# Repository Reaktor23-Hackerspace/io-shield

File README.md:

# IO-shield

IO-shield is a Arduino shield with 8 LED's, 8 push buttons and 2 potentiometers, designed for learning purposes.

# Pictures

# Example program

Open and upload the example program with the Arduino IDE. Each button triggers a LED blink pattern. 
The program is for test purposes to test all components on the board (except for the 2 potentiometers).

 - Button 1 : All LED's off
 - Button 2 : All LED's on
 - Button 3 : All LED's blink
 - Button 4 : Knightrider
 - Button 5 : Chaser
 - Button 6 : VU Meter
 - Button 7 : Random blink
 - Button 8 : Bounce

Note: You need to press the buttons for about 2 seconds in the worst case to trigger a pattern change.

# Wiring

 - Push button 1 : Arduino Pin 11
 - Push button 2 : Arduino Pin 10
 - Push button 2 : Arduino Pin 9
 - Push button 4 : Arduino Pin 8
 - Push button 5 : Arduino Pin 7
 - Push button 6 : Arduino Pin 6
 - Push button 7 : Arduino Pin 5
 - Push button 8 : Arduino Pin 4

 - LED 1 : Arduino Pin 3
 - LED 2 : Arduino Pin 2
 - LED 3 : Arduino Pin A0
 - LED 4 : Arduino Pin A1
 - LED 5 : Arduino Pin A2
 - LED 6 : Arduino Pin A3
 - LED 7 : Arduino Pin A4
 - LED 8 : Arduino Pin A5

# Partlist

## Reichelt

 Part name      | Part type                                                                    | Part price (EUR) 
--------------- | ---------------------------------------------------------------------------- | ---------------- 
LED1 - LED8     | [SMD-LED 3528 BL](http://www.reichelt.de/index.html?ACTION=3;ARTICLE=46297)  | 0.25 
R9 - R16        | [SMD 1/4W 220](http://www.reichelt.de/index.html?ACTION=3;ARTICLE=18287)     | 0.103
R1 - R8         | [SMD 1/4W 10K](http://www.reichelt.de/index.html?ACTION=3;ARTICLE=18244)     | 0.103
JP1 - JP16      | [SL 1X36G 2,54](http://www.reichelt.de/index.html?ACTION=3;ARTICLE=19504)    | 0.15
                | [JUMPER 2,54GL SW](http://www.reichelt.de/index.html?ACTION=3;ARTICLE=9019)  | 0.04
S1 - S8         | [TASTER 9314](http://www.reichelt.de/index.html?ACTION=3;ARTICLE=44510)      | 0.20

## dirtypcbs.com

- PCB 20Stk.        10x10cm + DHL HongKong = 75$ (58.88 EUR)

## Ebay

- Pin Header 6x                       0.15 EUR      2 pcs. / board
- Pin header 8x                       0.15 EUR      3 pcs. / board

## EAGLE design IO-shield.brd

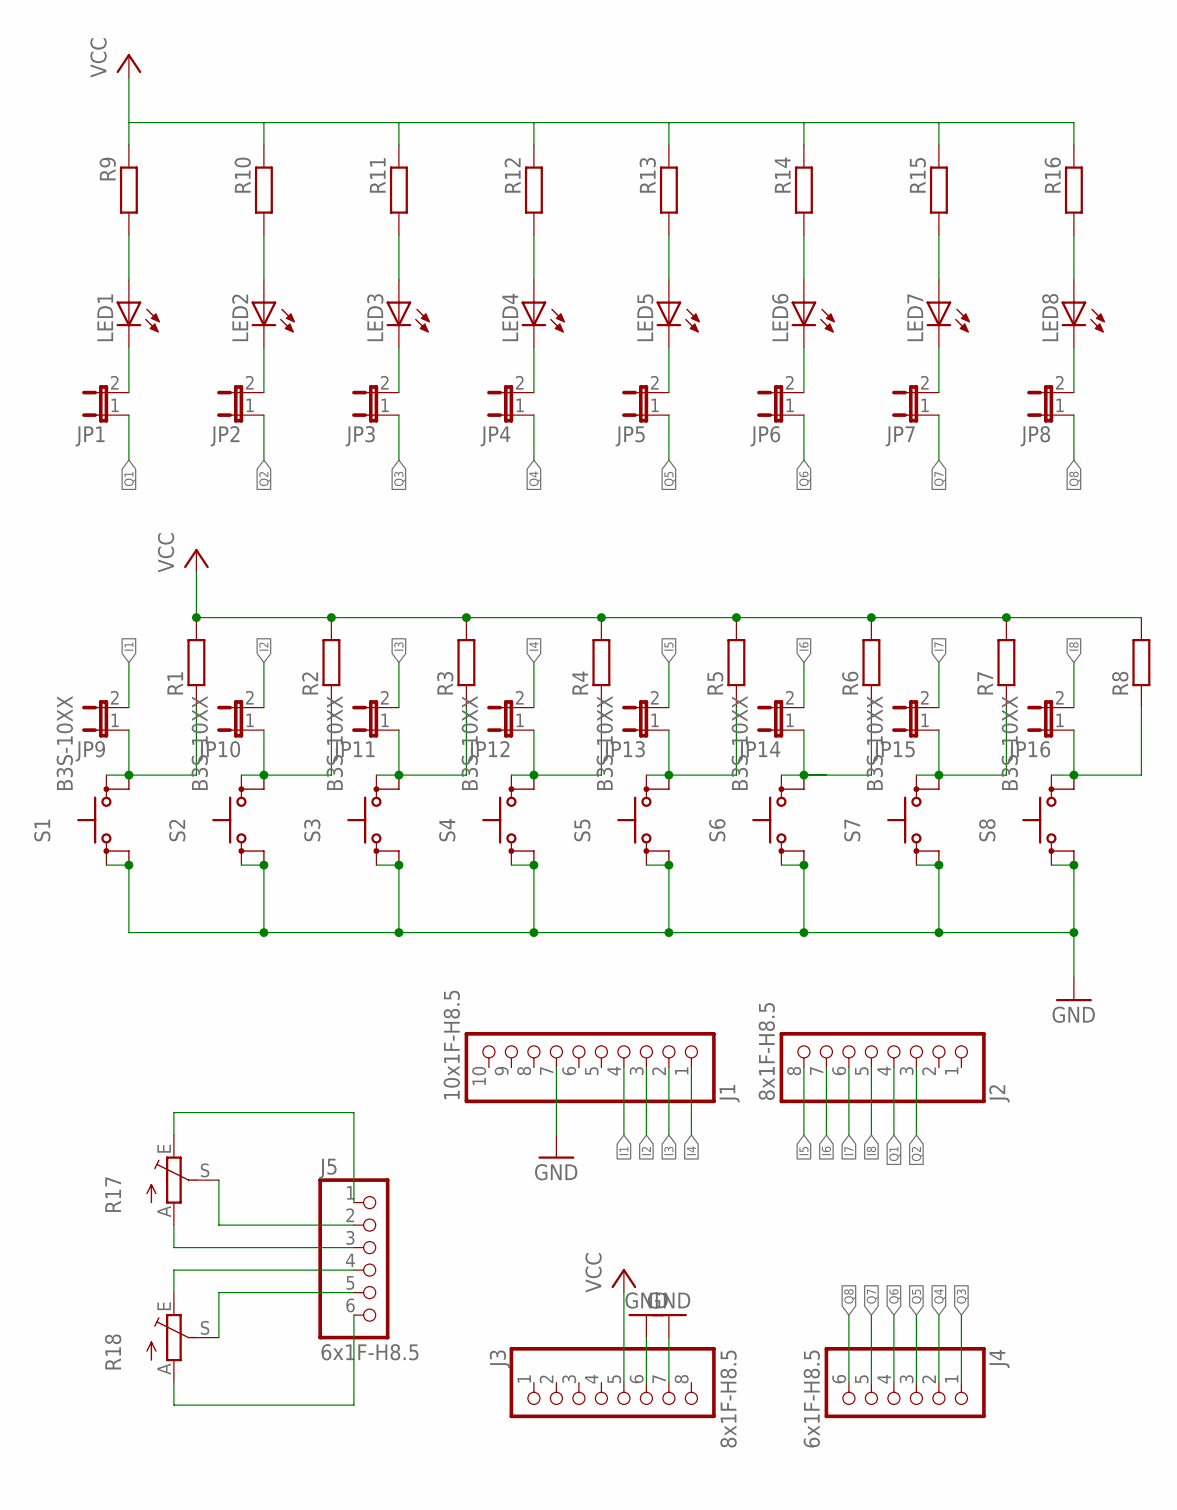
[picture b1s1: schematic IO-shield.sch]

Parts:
J1: 10x1F-H8.5; 1X10
J2, J3: 8x1F-H8.5; 1X08
J4, J5: 6x1F-H8.5; 1X06
JP1, JP2, JP3, JP4, JP5, JP6, JP7, JP8, JP9, JP10, JP11, JP12, JP13, JP14, JP15, JP16: JP1E; JP1
LED1, LED2, LED3, LED4, LED5, LED6, LED7, LED8: LEDKA-3528ASYC; KA-3528ASYC
R1, R2, R3, R4, R5, R6, R7, R8, R9, R10, R11, R12, R13, R14, R15, R16: R-EU_M1206; M1206
R17, R18: TRIM_EU-CA6V; CA6V
S1, S2, S3, S4, S5, S6, S7, S8: B3S-10XX

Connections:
GND: J1.7, J3.6, J3.7, S1.1, S1.2 (P1), S2.1, S2.2 (P1), S3.1, S3.2 (P1), S4.1, S4.2 (P1), S5.1, S5.2 (P1), S6.1, S6.2 (P1), S7.1, S7.2 (P1), S8.1, S8.2 (P1)
I1: J1.4, JP9.2
I2: J1.3, JP10.2
I3: J1.2, JP11.2
I4: J1.1, JP12.2
I5: J2.8, JP13.2
I6: J2.7, JP14.2
I7: J2.6, JP15.2
I8: J2.5, JP16.2
unnamed: JP1.2, LED1.C
unnamed: JP2.2, LED2.C
unnamed: JP9.1, R1.1, S1.3 (S), S1.4 (S1)
unnamed: JP10.1, R2.1, S2.3 (S), S2.4 (S1)
unnamed: JP11.1, R3.1, S3.3 (S), S3.4 (S1)
unnamed: JP12.1, R4.1, S4.3 (S), S4.4 (S1)
unnamed: JP13.1, R5.1, S5.3 (S), S5.4 (S1)
unnamed: JP14.1, R6.1, S6.3 (S), S6.4 (S1)
unnamed: LED1.A, R9.2
unnamed: LED2.A, R10.2
unnamed: LED3.A, R11.2
unnamed: LED4.A, R12.2
unnamed: LED5.A, R13.2
unnamed: LED6.A, R14.2
unnamed: LED7.A, R15.2
unnamed: LED8.A, R16.2
unnamed: JP15.1, R7.1, S7.3 (S), S7.4 (S1)
unnamed: JP16.1, R8.1, S8.3 (S), S8.4 (S1)
unnamed: JP3.2, LED3.C
unnamed: JP4.2, LED4.C
unnamed: JP5.2, LED5.C
unnamed: JP6.2, LED6.C
unnamed: JP7.2, LED7.C
unnamed: JP8.2, LED8.C
unnamed: J5.2, R17.S
unnamed: J5.1, R17.E
unnamed: J5.3, R17.A
unnamed: J5.5, R18.S
unnamed: J5.4, R18.E
unnamed: J5.6, R18.A
Q1: J2.4, JP1.1
Q2: J2.3, JP2.1
Q3: J4.1, JP3.1
Q4: J4.2, JP4.1
Q5: J4.3, JP5.1
Q6: J4.4, JP6.1
Q7: J4.5, JP7.1
Q8: J4.6, JP8.1
VCC: J3.5, R1.2, R2.2, R3.2, R4.2, R5.2, R6.2, R7.2, R8.2, R9.1, R10.1, R11.1, R12.1, R13.1, R14.1, R15.1, R16.1

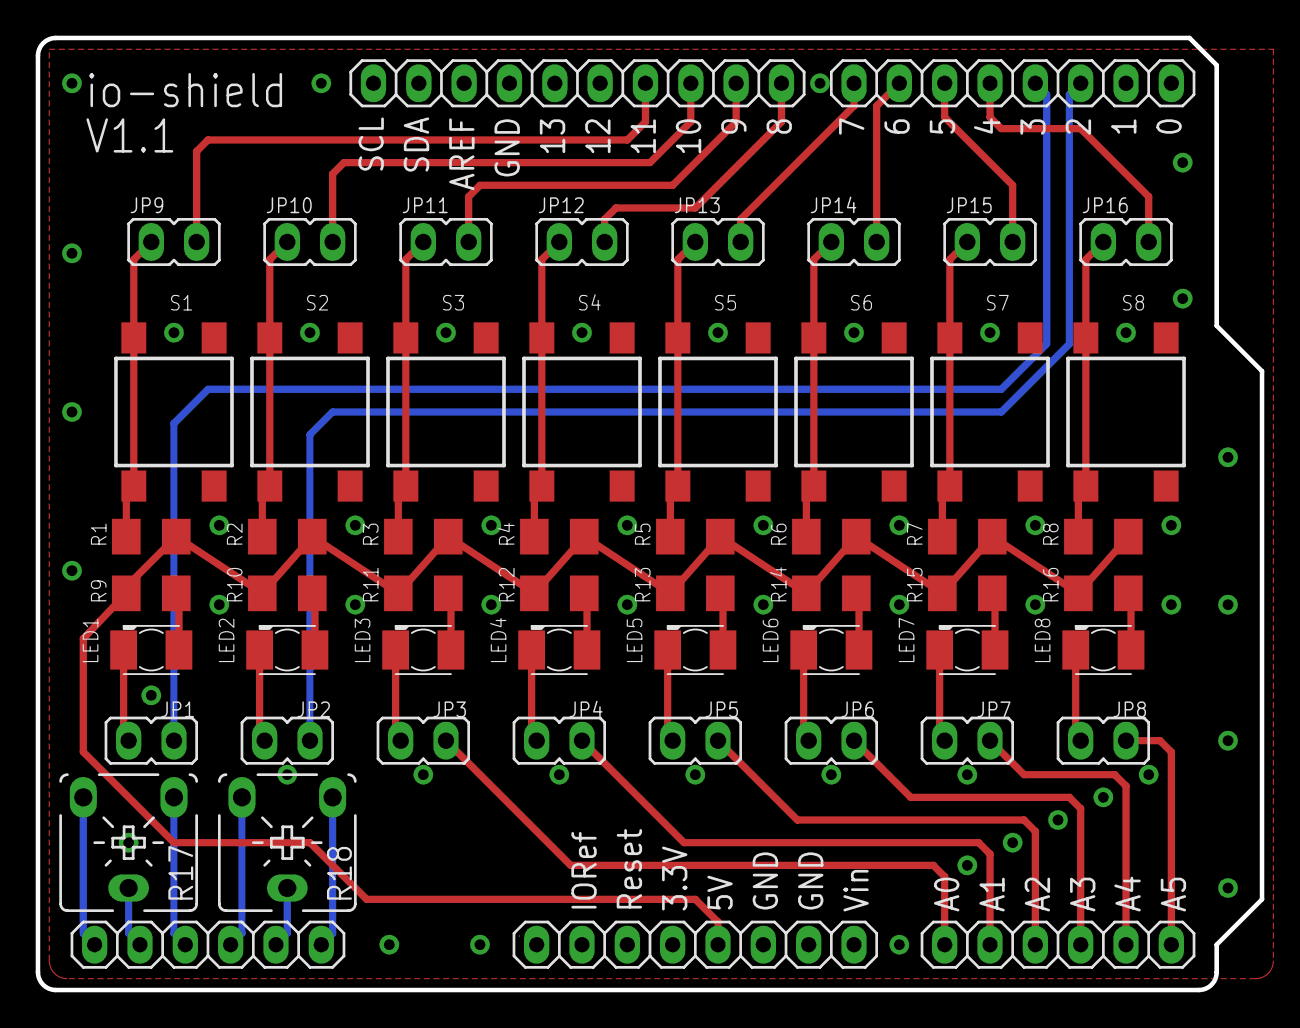
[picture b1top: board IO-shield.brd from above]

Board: 2 copper layers, 68.6 x 53.3 mm, 55 parts (0 on the bottom side), 48 nets.

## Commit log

2014-10-08 initial release
2014-10-29 extended shield with jumpers, added part list and picture
2014-11-06 changed position of the jumpers
2014-11-06 added 2 potis and header
2014-11-22 added code example
2014-11-24 added delay to random blink
2014-11-25 updated README, added eagle layout picture, fixed board silkscreen
2014-11-25 fixed image link in README$
2014-11-25 added a assambled picture
2014-11-25 cleaned the README a bit
